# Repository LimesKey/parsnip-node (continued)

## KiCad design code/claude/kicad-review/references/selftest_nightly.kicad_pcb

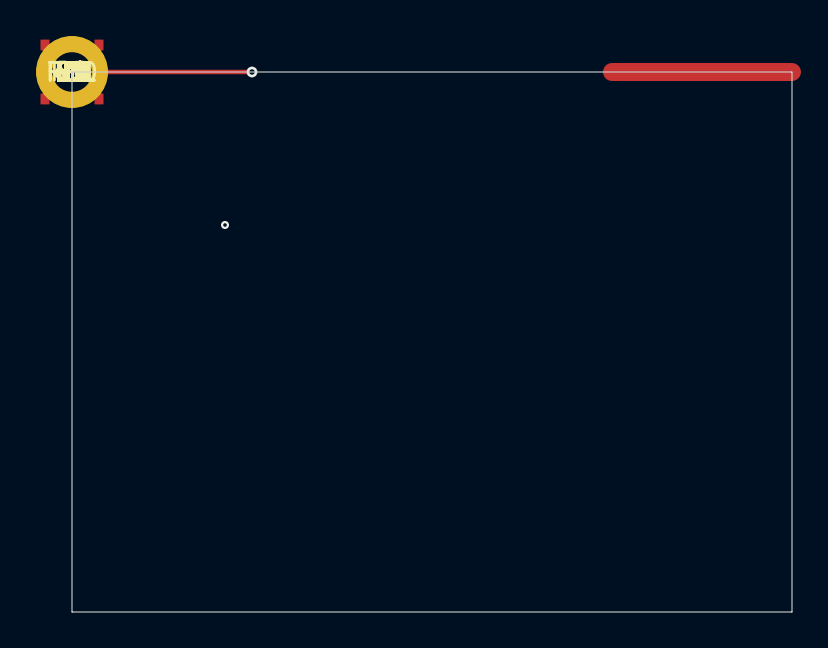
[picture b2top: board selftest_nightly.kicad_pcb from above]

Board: 2 copper layers, 40.0 x 30.0 mm, 20 parts (1 on the bottom side), 3 nets.

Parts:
C1: 100nF; FP
C2: 1uF; FP
C9: 10k; FP
D1: LED; FP
H1: MountingHole; MountingHole_2.2mm_M2_DIN965_Pad
J1, J3: HDR; PinHeader_1x02_P2.54mm_Vertical
J2: Conn_Coaxial; U.FL_Hirose_U.FL-R-SMT-1_Vertical
L1: 2.2uH; L_4x4mm
R1, R2, R9, R10, R11: 10k; FP
R3: 1k; FP
R4, R5: 0R; FP
TP1: TP; TestPoint_Pad_D1.5mm
U1: MCU_OK; FP
Y1: 32.768kHz; Crystal_SMD_3215-2Pin_3.2x1.5mm

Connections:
+3V3: C1.1, U1.1 (VDD)
GND: C1.2, C2.2, D1.2, J2.2, TP1.1, U1.2 (GND)
NB: R1.2, R2.1

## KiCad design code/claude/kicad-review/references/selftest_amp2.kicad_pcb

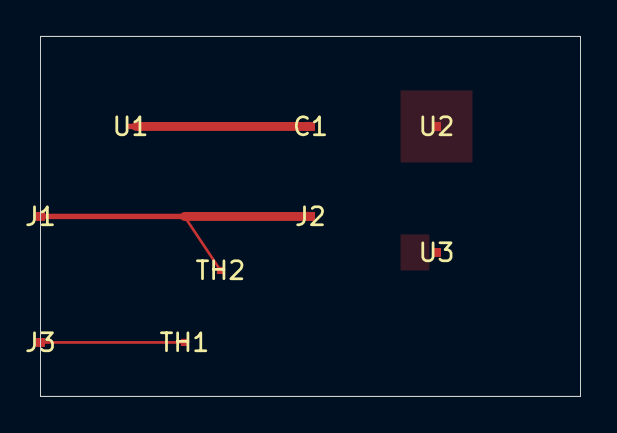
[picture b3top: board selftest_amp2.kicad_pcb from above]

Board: 2 copper layers, 30.0 x 20.0 mm, 9 parts (0 on the bottom side), 3 nets.

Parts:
C1: 10uF; FP
J1, J2, J3: HDR; FP
TH1, TH2: NTC10K; FP
U1: FINEPITCH; FP
U2: COVERED; FP
U3: GAPPED; FP

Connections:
ALLTAP: J3.1, TH1.1
NECK: C1.1, U1.1
TAP: J1.1, J2.1, TH2.1

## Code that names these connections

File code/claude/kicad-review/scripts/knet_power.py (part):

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_SW_PIN = re.compile(r'^(SW|LX|PH|BOOT|BST|CB)\d*$', re.I)
_SRC_NAME = re.compile(r'VBUS|SOLAR|VIN|VBAT|BATT?\b|PWR_IN|DC_?IN', re.I)
_IN_PIN = re.compile(r'^(P?VIN\d*|IN\d*|VBUS\w*|VAC\d+|BAT)$', re.I)
_OUT_PIN = re.compile(r'^(P?VOUT\d*|OUT\d*|SYS|SW\d*|LX\d*|PPHV|LDO_?\w*|BAT|PMID|REGN|VREG\w*)$', re.I)
_LOAD_PFX = ('U', 'IC', 'J', 'P', 'CN', 'Y', 'X', 'DS', 'M', 'BZ', 'LS', 'K')

def _ohms_le(value, lim):
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def c_powertree(nl, a):
    r = powertree_rows(nl, a.cfg)
    if r is None:
        print("no power source found (no BT cells, no connector pin named VBUS/SOLAR/VIN/BAT)"); return 1
    items, lost = r
    print(f"power tree from {sum(1 for it in items if it[0] == 'src')} source(s); volts are name-derived "
          f"(--rail/knet.json), Vout/ILIM from knet.json vref/ilim tables")
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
